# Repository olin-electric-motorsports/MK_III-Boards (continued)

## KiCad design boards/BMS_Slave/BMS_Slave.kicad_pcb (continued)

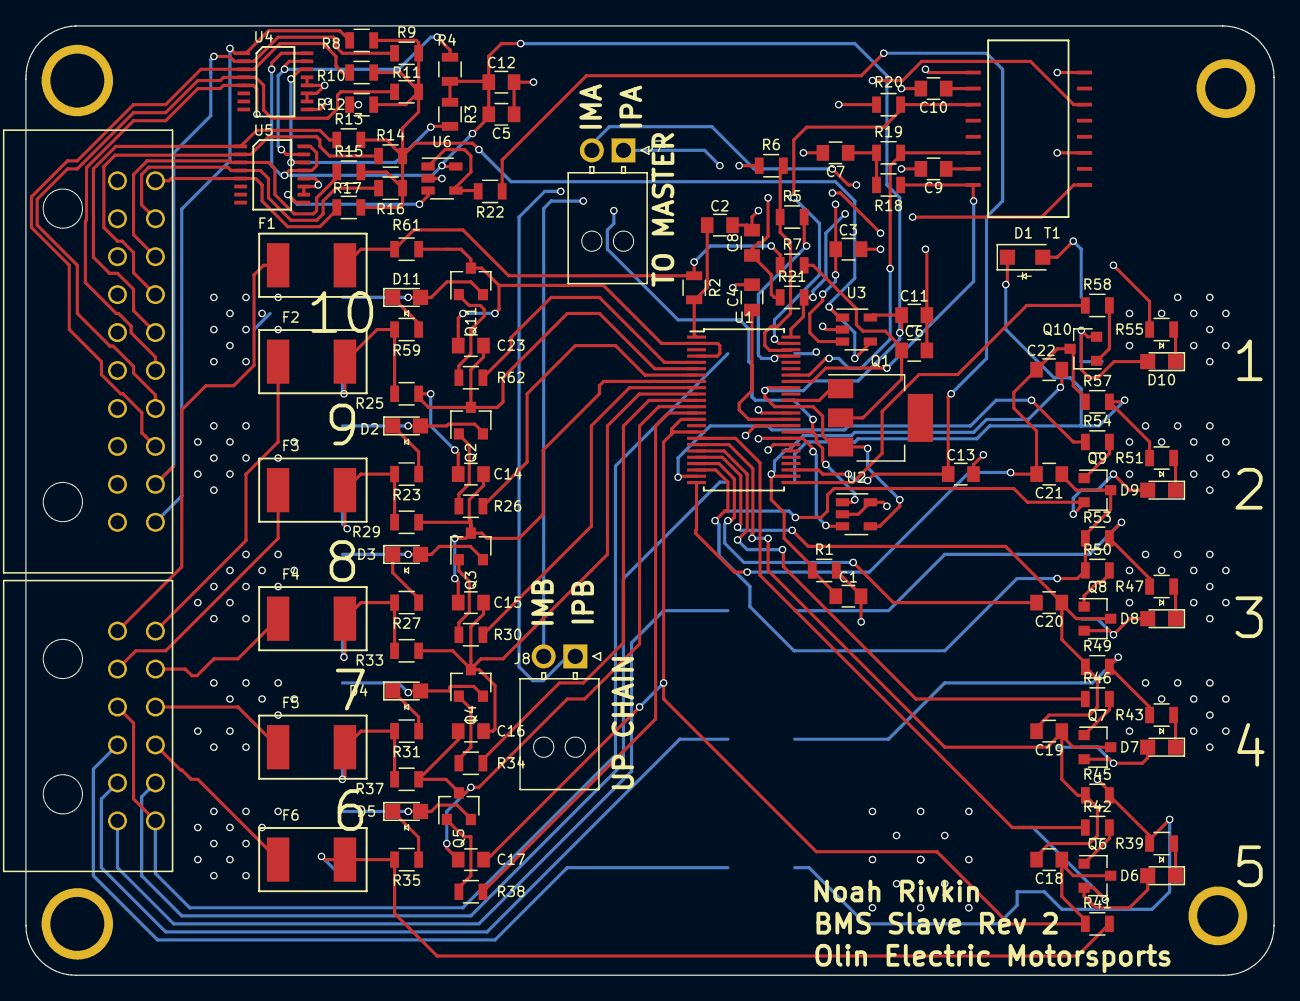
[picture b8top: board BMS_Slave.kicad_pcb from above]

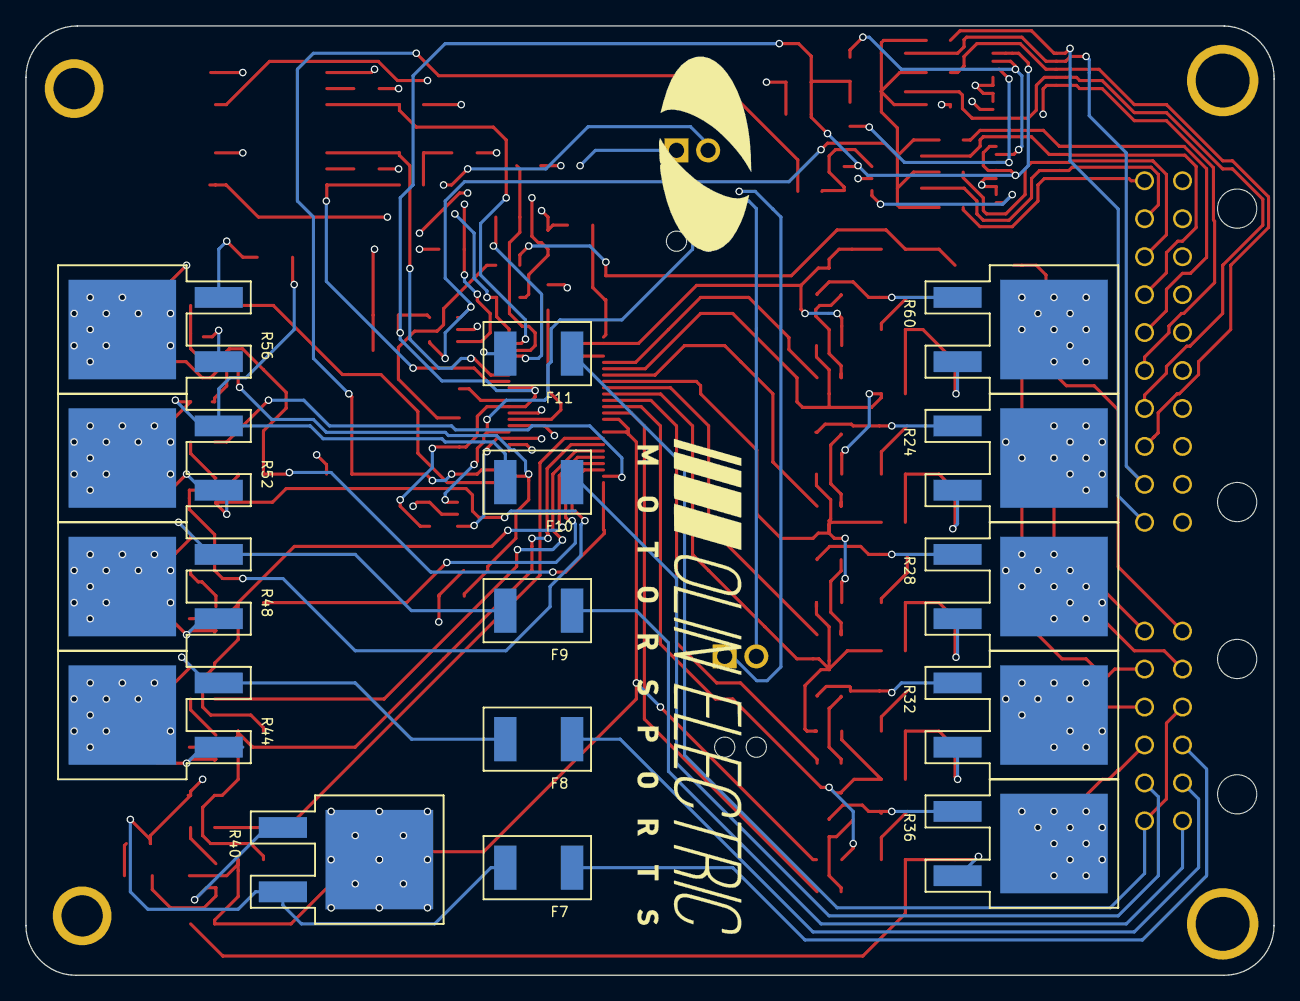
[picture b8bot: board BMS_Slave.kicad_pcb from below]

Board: 4 copper layers, 98.7 x 75.1 mm, 133 parts (15 on the bottom side), 109 nets.

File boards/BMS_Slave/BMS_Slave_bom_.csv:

Component,Description,Part,References,Value,Footprint,Quantity Per PCB,MPN
1,Unpolarized capacitor,C,C1 C7 C8 C9 C10 C13 C14 C15 C16 C17 C18 C19 C20 C21 C22 C23,10nF,C_0805_OEM,16,
2,Unpolarized capacitor,C,C3 C4 C5 C11 C12,1uF,C_0805_OEM,5,
3,Cap 50V 0.1uF 10% 0805,C_0.1uF,C2 C6,C_0.1uF,C_0805_OEM,2,478-3352-1-ND
4,DIODE SCHOTTKY 100V 1A SOD123,D_Schottky_SOD123,D1,D_Schottky_SOD123,D_SOD-123W_OEM,1,1727-2394-1-ND
5,LED_0805,LED_0805,D2 D3 D4 D5 D6 D7 D8 D9 D10 D11,LED_0805,LED_0805_OEM,10,475-1410-1-ND
6,,200mA_Fuse,F1 F2 F3 F4 F5 F6 F7 F8 F9 F10 F11,200mA_Fuse,Fuse_1812,11,
7,,MicroFit_12,J5,MicroFit_12,Microfit3_Header_02x06_Angled_OEM,1,
8,,MicroFit_20,J6,MicroFit_20,Molex_Microfit3_Header_02x10_Angled_OEM,1,
9,,NanoFit_2,J7 J8,NanoFit_2,Molex_NanoFit_1x02x2.50mm_Angled_OEM,2,
10,N-channel MOSFET,NMOS_GSD_30V,Q2 Q3 Q4 Q5 Q6 Q7 Q8 Q9 Q10 Q11,NMOS_GSD_30V,SOT-23F,10,SSM3K333RLFCT-ND
11,Transistor NPN (general),Q_NPN_BCE,Q1,Q_NPN_BCE,SOT-223,1,
12,Resistor,R,R26 R30 R34 R38 R42 R46 R50 R54 R58 R62,3.3k,R_0805_OEM,10,
13,Resistor,R,R3 R4,4.99k,R_0805_OEM,2,
14,Resistor,R,R18 R19 R20 R21,60.4,R_0805_OEM,4,
15,,DTO25,R24 R28 R32 R36 R40 R44 R48 R52 R56 R60,DTO25,DTO25,10,
16,Res 100 1%,R_100,R1 R2 R7 R22 R25 R29 R33 R37 R41 R45 R49 R53 R57 R61,R_100,R_0805_OEM,14,RNCP0805FTD100RCT-ND
17,Res 10k 1%,R_10k,R8 R9 R10 R11 R12 R13 R14 R15 R16 R17,R_10k,R_0805_OEM,10,CRS0805-FX-1002ELFCT-ND
18,Res 1k 1%,R_1k,R5 R6,R_1k,R_0805_OEM,2,RNCP0805FTD1K00CT-ND
19,Res 475 1%,R_475,R23 R27 R31 R35 R39 R43 R47 R51 R55 R59,R_475,R_0805_OEM,10,311-475CRCT-ND
20,,T_LAN_7490100111A,T1,T_LAN_7490100111A,7490100111A,1,
21,,24AA01,U2,24AA01,SOT-23-5_OEM,1,
22,,LTC1380,U4 U5,LTC1380,SSOP-16_LTC1380,2,
23,,LTC6811-1,U1,LTC6811-1,TSSOP-48_LTC6811-1,1,
24,"10 MHz, 850 µA Op Amps, SOT-23-5",MCP6001,U3 U6,MCP6001,SOT-23-5_OEM,2,

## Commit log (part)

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2017-10-17 balance schematic for BMS slave
2017-10-17 Added to bma slave
2017-10-19 added some text to the reference schematic
2017-10-20 IMD Latch 17-18 V1
2017-10-20 add AIL Kicad files such as schematics
2017-10-21 added more text and changed to net labels
2017-10-22 minor changes to template
2017-10-23 added and started working on demo project for talking about schematic capture and layout
2017-10-24 added demo board as example of good schematic and for the purpose and doing layout tutorial later
2017-10-24 BMS_Slave: added balancing sheets
2017-10-24 Added up to date files on the throttle and steering boards-20171023
2017-10-24 BMS_Slave: wired power and some of multiplexer
2017-10-25 Dashboard Schematic
2017-10-25 fixed ultrafit 2 with new component from josh's edit
2017-10-26 fix error on demo board from template schematic, generated netlist
2017-10-26 layout for demo board, no traces
2017-10-26 fixed footprints on demo board to have hidden value fields
2017-10-27 edited discharge circuit schematic
2017-10-27 Updated the steering-throttle schematic. Need to check footprints and create netlist before going to layout.
2017-10-28 Redesigned IMD Latch
2017-10-30 Layout Ready IMD Latch
2017-10-31 Adds BOM
2017-10-31 Starting Layout
2017-10-31 Added isoSPI parts and fuses
2017-10-31 Layout01
2017-11-01 Layout finished
2017-11-01 Traces fixed on first draft breakout board
2017-11-02 Minor changes to CP2120 breakout
2017-11-02 Tracing ready Layout
2017-11-03 Fixed dashboard schematic, added CP2120 breakout Gerber files
2017-11-03 BMS debugging, slave components added
2017-11-03 IMD Latch Tracing for the first time
2017-11-05 resetting
2017-11-05 Revert "working on layout for demo board"
    This reverts commit 3b03860be1fea2580bb2346a539b319ade0bb797.
2017-11-05 modified discharge circuit schematic
2017-11-05 Almost done with layout. Updated design rules
2017-11-05 BMS_Slave: began adding footprints
2017-11-06 add schematics for charging
2017-11-06 charging
2017-11-06 Added Molex connector footprints
2017-11-06 add pcb layout with tracing for AIL Precharge
2017-11-06 Started on routing for the board.
2017-11-07 Layout and routing for board version 1
2017-11-07 Created schematic for DTO25 test board
2017-11-08 preparing for v2
2017-11-10 DTO@% test board MKII
2017-11-10 Add TSAL designs up to DR 2
2017-11-10 add finalized pcb, schematics, gerber and drill files for AIL_Precharge
2017-11-10 Created Gerber files for DTO25 test board
2017-11-11 modified discharge circuit
2017-11-11 pull down for IMD output
2017-11-12 IMD Latch V2 Layout
2017-11-12 added traces to discharge circuit layout
2017-11-14 IMD Latch v2 not yet checked off
2017-11-14 added footprints for bms slave, nanofit for bms master
2017-11-14 new hand drawn schematics
2017-11-14 Finished PCB Layout for TO-263-Test board
2017-11-14 Round two for routing on board.
2017-11-17 modified connectors on HV schematic
2017-11-17 BMS_Slave: All parts have appropriate footprints from OEM library
2017-11-17 Adding TSAL board schematic
2017-11-17 BMS Slave: began layout
2017-11-17 Adding changes to the TO-263 Test board
2017-11-17 Finished & Shipped IMD Latch v2
2017-11-17 Final drawing for routing. Pending final check-off
2017-11-17 generating BOM for demo board
2017-11-20 finished demo board and added silk screen
2017-11-22 added gordon's dxf files to the main repo
2017-11-22 got rid of my original dxfs
2017-11-22 Last changed on board submited to be shipped. V1.0
2017-11-22 fixed design rules on template
2017-11-23 added Brake Light board
2017-11-23 early version of layout
2017-11-23 started working on interface protoboard
2017-11-24 Adding TSAL 1.0 with gerber and drill files in PostScript format
2017-11-24 Adding gerbers zip file
2017-11-27 fixed repo and added current versions of BMS, BMS_slave, and DTO25 test board
2017-11-28 BSPD folder
2017-11-28 finish tracing for suspension strain sensing board
2017-11-28 Adding AIR Control Board
2017-11-30 created bom for demo board with josh's new instructions
2017-12-01 added gerber files for discharge circuit
2017-12-01 3D Model
2017-12-01 BMS: created and assigned all footprints, began rough layout
2017-12-01 updated schemetic and layout
2017-12-02 Shipped IMD Latch v2 with 3D Model
2017-12-04 Updated PCB Layout 11-4
2017-12-04 started on the throttle-steering position interface board.
2017-12-05 BMS: added sutdown control sense on micromatch pin 12
2017-12-05 Corrected pin out
2017-12-08 Add pdf for Pup's viewing pleasure
2017-12-08 BMS_Slave: first pass layout
2017-12-09 deleting BSPD folder
2017-12-09 Reuploaded BSPD folder
2017-12-12 adding AIR folder
2017-12-12 BMS Slave: around 1/2 of layout and tracing done
2017-12-15 final version of suspension strain
2017-12-15 BMS Slave: added inner layers, traced 1/2 of balancers.
2017-12-16 Final PCB
2017-12-18 Fixed wrong footprint.
2017-12-21 Final PCB V1 with gerbers and BOM
2017-12-24 BMS Slave: began tracing.
2017-12-25 BMS Slave: completed tracing and layout
2017-12-26 BMS Slave: Added therrmal vias, moved designators
2017-12-27 added bom to dc and changed things on hv interface (old edit)
2017-12-27 added 3d components to board
2017-12-28 added a 3d step model of the dc board
2017-12-28 AIR Control (for brycemann8334 repo)
2018-01-02 started IMD Latch v3
2018-01-02 Adding new boards LED bar backpack and internal interface
2018-01-03 Adding TSAL v2
2018-01-04 Prettified the circuit
2018-01-04 generated BMS slave gerber files
2018-01-04 Added the optocoupler
2018-01-04 Labeling for ESF
2018-01-05 Flipped the MOSFET
2018-01-06 BMS Slave:Fixed step file and added 3d models
2018-01-08 Restored original air folder
2018-01-13 Progress
2018-01-14 IMD v3 with layout
2018-01-15 IMD Latch v3 for review
2018-01-16 BMS_Slave: added BoM
2018-01-17 Deleted and re-cloned repo
2018-01-18 Fixing merge errors
2018-01-20 Gerber and BOM files for functional board
2018-01-22 Edited interface boards
2018-01-25 Updated info for BOM
2018-01-26 fixed a typo in schematic
2018-01-26 Temp @Utsav
2018-01-26 modifying discharge circuit to fit in accumulator
2018-01-26 Internal Interface
2018-01-26 Update of Board Files
2018-01-30 BMS: update file
2018-02-02 BMS Slave: updated BOM
2018-02-02 BMS: current sensor added
2018-02-02 IMD Latch connector redesigned
2018-02-02 Add i2c sub-schematic using ATmega328p
2018-02-02 Started schematic for LV interface board
2018-02-03 added layout and tracing for the discharge board
2018-02-03 Modified Backpack
2018-02-04 added revisions to discharge circuit
2018-02-04 one more revision
2018-02-04 adding PCB and schematic pdf
2018-02-04 adding cad to the repo
2018-02-04 added gerber files to discharge circuit
2018-02-04 added more connections to the accumulator schematic
2018-02-04 fixed micromatch 6 on demo board
2018-02-04 Final TSAL v2 schematic
2018-02-04 Updated schematic with Atmega 16 instead of cp2120
2018-02-04 Worked on wheel speed schematic
2018-02-05 updated air control schematic, going to work on layout soon
2018-02-05 A bit more work on the schematic
2018-02-05 Adding TSAL v2 final schematic
2018-02-05 Started layout
2018-02-05 fixed schematic
2018-02-06 Added bypass capacitors to op-amp and extra HF caps to buck converter
2018-02-06 fix tracks for shutdown circuit
2018-02-06 working on AIR control board, starting layout
2018-02-06 final revisions to discharge board
2018-02-06 schematic is maybe done
2018-02-06 add CAD for precharge
2018-02-06 Updated Layout (added bypass cap to Brake Light Circuit), continued with layout, and started tracing modules
2018-02-06 BOM, Netlist, PCB final
2018-02-06 made discharge smaller
2018-02-06 Solved 2 errors
2018-02-06 Hopefully finalised
2018-02-06 Made changes to resolve merge conflicts
2018-02-07 preparng for merge
2018-02-07 Added PDFs of Schematic and PCB
2018-02-07 Added 1.43k res for AIL
2018-02-07 Forgot to save the file
2018-02-08 added bypass caps to BSPD, edited LV interface sch
2018-02-08 rough draft of completed LV interface sch
2018-02-09 BMS: Layout, tracing, and fabrication outputs
2018-02-09 add accumulator connector
2018-02-09 added 3d models to discharge board
2018-02-11 Rev 2 files for throttle-steering
2018-02-12 Worked on layout, almost done unless the traces are really bad
2018-02-12 Updated Layout
2018-02-13 fixed some issues with template schematic
2018-02-13 BMS Slave: changed NanoFit direction for mechanical
2018-02-13 edited lv interface board
2018-02-13 Started logger board, updated interface
2018-02-13 added traces to accumulator
2018-02-14 Final dashboard L interface revision.
2018-02-15 finished layout for air ctrl board, starting tracing
2018-02-15 finished routing, need dxf and then pcb design checklist of air ctrl board
2018-02-16 started cad, I am having to change the paths for 3D models for components
2018-02-16 finished air ctrl board, need to go through pcb design checklist
2018-02-16 Finished layout and tracing, passed design rule check
2018-02-17 finished air ctrl board, need to export gerbers and bom
2018-02-17 Modified layout for accumulator board.
2018-02-19 exported gerbers, bom and pdfs for air ctrl board. switching to ubuntu to export CAD
2018-02-19 Accum Update
2018-02-20 Boards updated
2018-02-20 saving before trying something that can't be undone
2018-02-20 Gerbers and PDFs
2018-02-20 checking off lv interface sch
2018-02-20 board cad and updated gerbers for air ctrl board
2018-02-20 updated footprint matching, schematic fully checked off
2018-02-20 Fixing merge conflicts
2018-02-20 Fixing more merge conflicts
2018-02-21 working on LV interface layout, added measurements to LV box boards to accurately place connectors
2018-02-21 finalized micromatch locations
2018-02-22 finished layout for lv interface, adding CAD now and switching to ubuntu to export board CAD for mechanical
2018-02-22 made step files for led bar components
2018-02-22 finished CAD, fixed fuse block footprint
2018-02-23 Gerbers and boms
2018-02-23 created BOMs, misc
2018-02-23 finished cad
2018-02-23 Updated pdfs
2018-02-24 Added CAD for Brake_Light_Shutdown_Sensing
2018-02-24 fixed traces and tried to make them look better
2018-02-24 Finished logger board, added some things
2018-02-26 added pdfs sorry
2018-02-26 improved routing
2018-02-27 fixed more tracing
2018-02-28 This totally counts as afternoon
2018-02-28 saving progress before switching strain and sensor pins
2018-02-28 shifted sensor and gauge pins around on Ampseal 2
2018-03-01 completed routing
2018-03-02 finished accumulator interface
2018-03-02 BMS Slave: Changed orientation of connectors
2018-03-03 updating remaining pdfs
2018-03-03 REAL final tracing
2018-03-03 new gerber files! fixed traces! PDF images!
2018-03-06 BMS Slave: Added CAD and updated Gerbers
2018-03-06 fab files forlv interface
2018-03-09 Final charging with gerber
2018-03-09 Charging-Final-3.08
2018-03-09 fixed discharge circuit
2018-03-10 Charing wGerber-checkedoff
2018-03-10 Updated External Interface
2018-03-10 Updatec External Interface
2018-03-26 attempt 2 to fix issues with drill files for pcbway
2018-03-27 External Interface Update
2018-03-28 BMS_Slave: updated tracing/connector for temp sense
2018-03-30 Added pdf for schematic and changed connnector positions
2018-03-30 BMS: added pdf of schematic
2018-03-31 fixed fuse block parameters
2018-03-31 BMS Slave: added silkscreen indicatind which cell is which LED
2018-03-31 Updated sch and pcb to fix +5V and add Brake_Light- pin to atmega
2018-04-08 zipped gerbers together for ordering
2018-04-13 BMS Slave: corrected mosfet routing
2018-04-17 trying to fix merge conflicts
2018-04-17 Revert "testing"
2018-04-17 replaced all files besides BMS with most updated files from upstream
2018-04-19 Revising TSAL
2018-04-24 Adding TSAL 2.1
2018-04-27 BMS Slave: Gerbers and pdf generated
2018-05-01 redid charging schematic
2018-05-01 fixed precharge layout
2018-05-02 minor charging routing update
2018-05-02 minor charging routing update2
2018-05-11 updated LV box interface to fix programming, fuse block and improve labelling
2018-08-13 images of buck schematic for linking in wiki
2018-08-13 adding pic for wiki
2018-11-03 Allocate PDFs into one folder
    The amount of times I had to type "cd" to get to one PDF was absurd
